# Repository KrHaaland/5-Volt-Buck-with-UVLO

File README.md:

# 5 Volt Buck with UVLO

A small 12 V to 5 V USB power adapter with an adjustable under-voltage lockout (UVLO),
built around the TI **TPS62933** 3 A synchronous buck converter.

It is meant for 12 V lead-acid systems (car, boat, cabin). The 5 V output switches off
when the battery sags to roughly 12.2 V and does not come back until the battery is being
charged again (roughly 13.3 V), so the adapter cannot flatten the battery.

The KiCad project files are named `USB-Adapter`.

## Specifications (as built)

| | |
|---|---|
| Input | 12 V nominal, Wago 2060-452 push-in terminal (J1). Converter range 3.8 V to 30 V. |
| Output | 5.16 V measured, USB-A receptacle (J2, TE 292303-1). Converter limit 3 A. |
| UVLO | Off at 12.1 to 12.3 V, on again at 13.3 to 13.4 V (measured, see tuning log) |
| Switching frequency | 500 kHz. The RT pin is left floating: the R3 footprint between RT and GND is not populated. Fitting a 0 Ω there would select 1.2 MHz. |
| Efficiency | About 95 % theoretical for 12 V in, 5 V out, based on the TPS62933 datasheet efficiency curves. Not yet measured on this board. |
| Inductor | Würth 74439387068, WE-XHMI 7070, 6.8 µH |
| Soft start | C4 on the SS pin |
| Board | 40 × 18 mm, 2 layers |

## Resistor values: read this before building

**The resistor values in the schematic and in the exported BOM under `production/` are
not the values on the working boards.** The first boards were built with 5 % resistors,
which turned out to be too loose for both dividers, so the values were tuned by measuring
and swapping. The table below is the as-built, tested configuration.

| Function | Refs | As built (tested) | Schematic | `production/bom.csv` |
|---|---|---|---|---|
| UVLO divider (VIN → EN → GND) | R1 / R2 | **530 kΩ / 53 kΩ** | 330 kΩ / 33 kΩ | 511 kΩ / 88.7 kΩ |
| Output voltage (VBUS → FB → GND) | R6 / R7 | **130 kΩ / 24 kΩ** | 43 kΩ / 8.2 kΩ | 53.6 kΩ / 10.2 kΩ |

**Use 1 % resistors.** With 1 % parts the as-built values should land on target
without the tweaking described below. The 5 % parts used so far needed measuring and
testing against the specific batch.

### Output voltage (R6 / R7)

The TPS62933 regulates the FB pin to 0.8 V:

```
V_OUT = 0.8 V × (1 + R6 / R7)
130 kΩ / 24 kΩ  →  5.13 V calculated, 5.16 V measured
```

The output is deliberately a little above 5.00 V to make up for voltage drop in the
USB cable. USB allows 4.75 V to 5.25 V at the connector.

### Under-voltage lockout (R1 / R2)

The EN pin has a 1.21 V rising and 1.17 V falling threshold (typical). It also has an
internal pull-up of 0.7 µA that is always present, plus an extra 1.4 µA once the device
is enabled. That extra current is what creates the hysteresis across R1:

```
V_START ≈ 1.21 V × (R1 + R2) / R2  −  0.7 µA × R1
V_STOP  ≈ 1.17 V × (R1 + R2) / R2  −  2.1 µA × R1

530 kΩ / 53 kΩ  →  V_START ≈ 12.9 V, V_STOP ≈ 11.8 V (typical values)
```

Measured boards sit 0.3 to 0.5 V above these calculated numbers. That is consistent with
the EN threshold spread in the datasheet (rising threshold up to 1.28 V max) combined
with 5 % resistors. The hysteresis is about 1.1 V; the datasheet recommends more than
0.5 V.

**Disabling the UVLO:** leave out (or remove) R1 and R2. The EN pin then floats and the
converter's internal pull-up current enables it, so it simply runs over the chip's full
3.8 V to 30 V input range.

## Tuning log

Notes from bring-up of the first two boards, all with 5 % resistors.

### UVLO (R1 / R2)

| R1 / R2 | Cuts off at | Activates again at |
|---|---|---|
| 330 kΩ / 33 kΩ | 12.6 V | 13.4 V |
| 560 kΩ / 56 kΩ, board 1 | 12.3 V | 13.36 V |
| 560 kΩ / 56 kΩ, board 2 | 12.14 V | 13.31 V |

560 kΩ / 56 kΩ was used instead of 330 kΩ / 33 kΩ.

### Output voltage (R6 / R7)

| Try | R6 / R7 | Calculated | Measured | Note |
|---|---|---|---|---|
| 1 | 43 kΩ / 8.2 kΩ | 5.00 V | 4.88 V | Too low. |
| 2 | 56 kΩ / 10 kΩ | 5.28 V | 5.23 V | A bit much, should be lowered. |
| 3 | 82 kΩ / 15 kΩ | 5.17 V | 5.17 V | Fine. |
| 4 | 130 kΩ / 24 kΩ | 5.13 V | 5.16 V | Better. |
| 5 | 300 kΩ / 56 kΩ | 5.09 V | 5.22 V | |
| 6 | 130 kΩ / 24 kΩ | 5.13 V | 5.16 V | Went back to this. Good enough. |

The plan is to get 1 % resistors. The 5 % ones require tweaking and testing with the
specific batch.

## 3D-printed case

A two-part enclosure generated from the PCB geometry, in `case/`:

- `usb-adapter-case.step`: base and lid in print orientation (lid upside down). Also as
  `usb-adapter-case-base.stl` and `usb-adapter-case-lid.stl` for slicing.
- `usb-adapter-case-base.step` and `usb-adapter-case-lid.step`: the two parts as separate files,
  same print orientation.
- `usb-adapter-assembly.step`: the complete unit as a STEP assembly: case (base, lid, three screws)
  and the populated board, every part named by its reference designator (J1, J2, L1, U1, C1 to C11,
  R1 to R7). R3 is left out because that footprint is not populated. Open this one to see how it
  all goes together.
- `usb-adapter-case-assembled.step`: base, lid and the three screws only, in their closed positions.
- `make_case.py`: the parametric FreeCAD script that produced the files. It reads the populated
  board from `USB-Adapter.step` in the repository root (the KiCad STEP export), removes everything
  below the board bottom because the pins are cut flush, and checks every component against base
  and lid. Edit the parameter block at the top and re-run with `freecadcmd` to change clearances,
  wall thickness and so on.

| | |
|---|---|
| Outer size | 64.2 × 22.8 × 15.2 mm, 2 mm walls (3.9 mm at the USB end), 2.6 mm floor, 2 mm lid plate with a solid fill down to 2.2 mm above the board |
| Board clearance | 0.4 mm to the side walls, no standoff: the board lies directly on the floor (the through-hole pins are trimmed flush). Over the board the lid is solid down to 2.2 mm above the board top, 0.6 mm above the 1.6 mm tall 1206 capacitors, with pockets 0.5 mm larger than the Wago, the inductor (as a 7070 envelope) and the USB shell; the Wago pocket is open towards the cable chamber for the wires. Printed upside down the pockets face up, so the lid still needs no supports. The two lid bosses beside the Wago are flattened on the connector side up to its height, leaving 0.45 mm. |
| Board position | After the first fit check the board was moved 0.5 mm towards the cable end relative to the box (`BOARD_DX` in the script): the three screw positions and the board stops sit 0.5 mm closer to the cable hole than the KiCad hole positions, which closes the gap between the USB flange and the end wall by the same amount. |
| USB end | U-shaped slot in the end wall; the lid carries a tab that closes the slot above the shell. Around the shell the slot is cut to the shell's nominal section (no clearance in the model: the second print measured almost 1 mm of gap per side with 0.5 mm, so the walls were brought 0.5 mm closer). From 0.2 mm below the tab's underside upwards the slot is 0.5 mm wider per side for the tab, so a lid printed before this change still fits. The wall reaches the connector's front flange, stopping 0.3 mm short of it, so only the flange shows outside the case. The shell's side latch tabs sit in a groove inside the wall. |
| Wire end | The cavity extends 17.5 mm beyond the board edge. A single 7.5 mm hole in the end wall takes a two-core cable, its lower edge 1.5 mm above the floor; the lid's locating lip is notched above the hole so a full-size cable clears it. The extension is free space for a zip tie cinched on the cable: the tie is bigger than the hole, so a yank on the cable stops at the tie instead of at the Wago connection. Two low ribs stop the board sliding into the extension. |
| Fastening | Three M2 × 6 hex-socket pan-head screws driven from below. Each passes through a 2.2 mm hole in the floor, through a 3 mm board hole, and self-taps into a 1.6 mm pilot hole in a boss that hangs from the lid down to the board, so the board is clamped between floor and boss. With a 6 mm screw 3.3 mm of thread sits in the boss; a 5 mm screw would give 2.3 mm. Use the 6 mm ones. The heads sit in 4.2 × 1.5 mm counterbores (0.1 mm deeper than the 1.4 mm head, since the printed overhang otherwise keeps the head slightly proud), flush with the bottom face and with 1.1 mm of floor above them, so the case stands flat. The lid locates with an inner lip before the screws go in. The screws are included in the assembled STEP. |

Assembly: feed the cable through the end wall, cinch a zip tie on it inside the extension,
strip the two conductors and push them into the Wago. Drop the board into the base so the USB
shell slides down into the end slot, fit the lid, and drive the three screws from underneath. Every part of the exported board (`USB-Adapter.step`, pins cut flush) was checked against base and
lid: no overlaps; the USB shell sits in a slot of its own nominal size (0 mm in the model, about
0.5 mm as printed), the flange is 0.3 mm from the end wall by design, and the lid bosses beside the
Wago have 0.45 mm. The inductor is checked as a 7070 envelope because the
KiCad model on the board is the smaller 6060 package. The first fit check showed the USB flange
sitting 0.5 mm further from the end wall than the model, so the model now places the USB shell
0.5 mm further out on the board (`USB_DX`) and the board 0.5 mm towards the cable end (`BOARD_DX`).

## Repository contents

- `USB-Adapter.kicad_pro`, `.kicad_sch`, `.kicad_pcb`: KiCad project, schematic and board.
- `USB-Adapter.step`: STEP export of the populated board from KiCad; the case script reads it.
- `schematic.pdf`: plotted schematic.
- `images/`: photo of the assembled board and a 3D render.
- `case/`: 3D-printable enclosure (STEP, STL, previews) and the FreeCAD script that generates it.
- `production/`: JLCPCB export from the Fabrication Toolkit plugin (gerber zip, BOM,
  component positions, IPC netlist). This export is from an earlier revision: besides the
  resistor values above, it lists C4 as 33 nF while the schematic has 100 nF, and it lists R3
  as 0 Ω although that footprint is left unpopulated on the boards.
- `fabrication-toolkit-options.json`: settings used for the export.

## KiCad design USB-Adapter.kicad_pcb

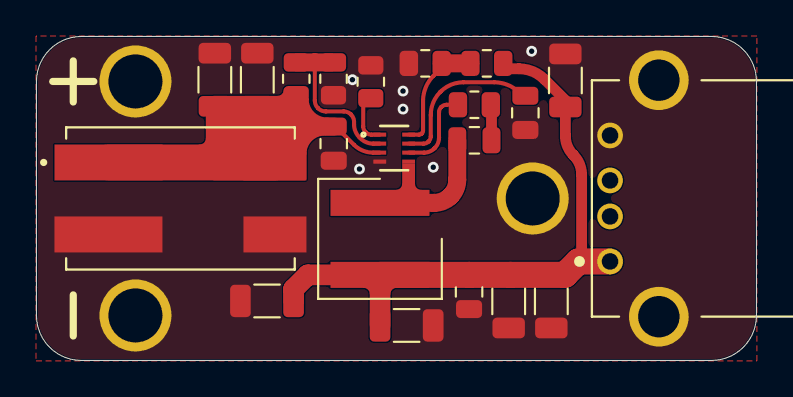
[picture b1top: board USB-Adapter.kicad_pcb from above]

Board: 2 copper layers, 40.0 x 18.0 mm, 21 parts (0 on the bottom side), 10 nets.

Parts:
C1, C2, C6, C7, C9, C10, C11: 10uF; C_1206_3216Metric
C3, C5, C8: 100nF; C_0805_2012Metric
C4: 33nF; C_0805_2012Metric
J1: Wago 2060-452
J2: 292303-1
L1: 7070_74439387068; 744393465068
R1: 511K; R_0805_2012Metric
R2: 88.7K; R_0805_2012Metric
R3, R4: 0 ohm; R_0805_2012Metric
R6: 53.6k; R_0805_2012Metric
R7: 10.2k; R_0805_2012Metric
U1: TPS62933DRLR; TPS62933

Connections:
GND: C1.2, C2.2, C3.1, C4.2, C6.2, C7.2, C8.1, C9.2, C10.2, C11.2, J1.2, J2.4 (GND), J2.SH1, J2.SH2, R2.2, R3.2, R7.1, U1.4 (GND)
unnamed: C5.1, R4.2
unnamed: C6.1, C7.1, C8.2, C9.1, C10.1, C11.1, J2.1 (VBUS), L1.2, R6.2
unnamed: R4.1, U1.6 (BST)
unnamed: R1.2, R2.1, U1.2 (EN)
unnamed: R6.1, R7.2, U1.8 (FB)
unnamed: R3.1, U1.1 (RT)
unnamed: C4.1, U1.7 (SS)
unnamed: C5.2, L1.1, U1.5 (SW)
unnamed: C1.1, C2.1, C3.2, J1.1, R1.1, U1.3 (VIN)

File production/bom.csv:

Designator,Footprint,Quantity,Value,LCSC Part #
"_3, _2, ",,3,,
"C1, C10, C11, C2, C6, C7, C9",1206,7,10uF,
"C3, C5, C8",0805,3,100nF,
C4,0805,1,33nF,
J1,Wago 2060-452,1,Wago 2060-452,C2765055
J2,292303-1,1,292303-1,
L1,744393465068,1,7070_74439387068,
R1,0805,1,511K,
R2,0805,1,88.7K,
"R3, R4",0805,2,0 ohm,
R6,0805,1,53.6k,
R7,0805,1,10.2k,
U1,TPS62933,1,TPS62933DRLR,
